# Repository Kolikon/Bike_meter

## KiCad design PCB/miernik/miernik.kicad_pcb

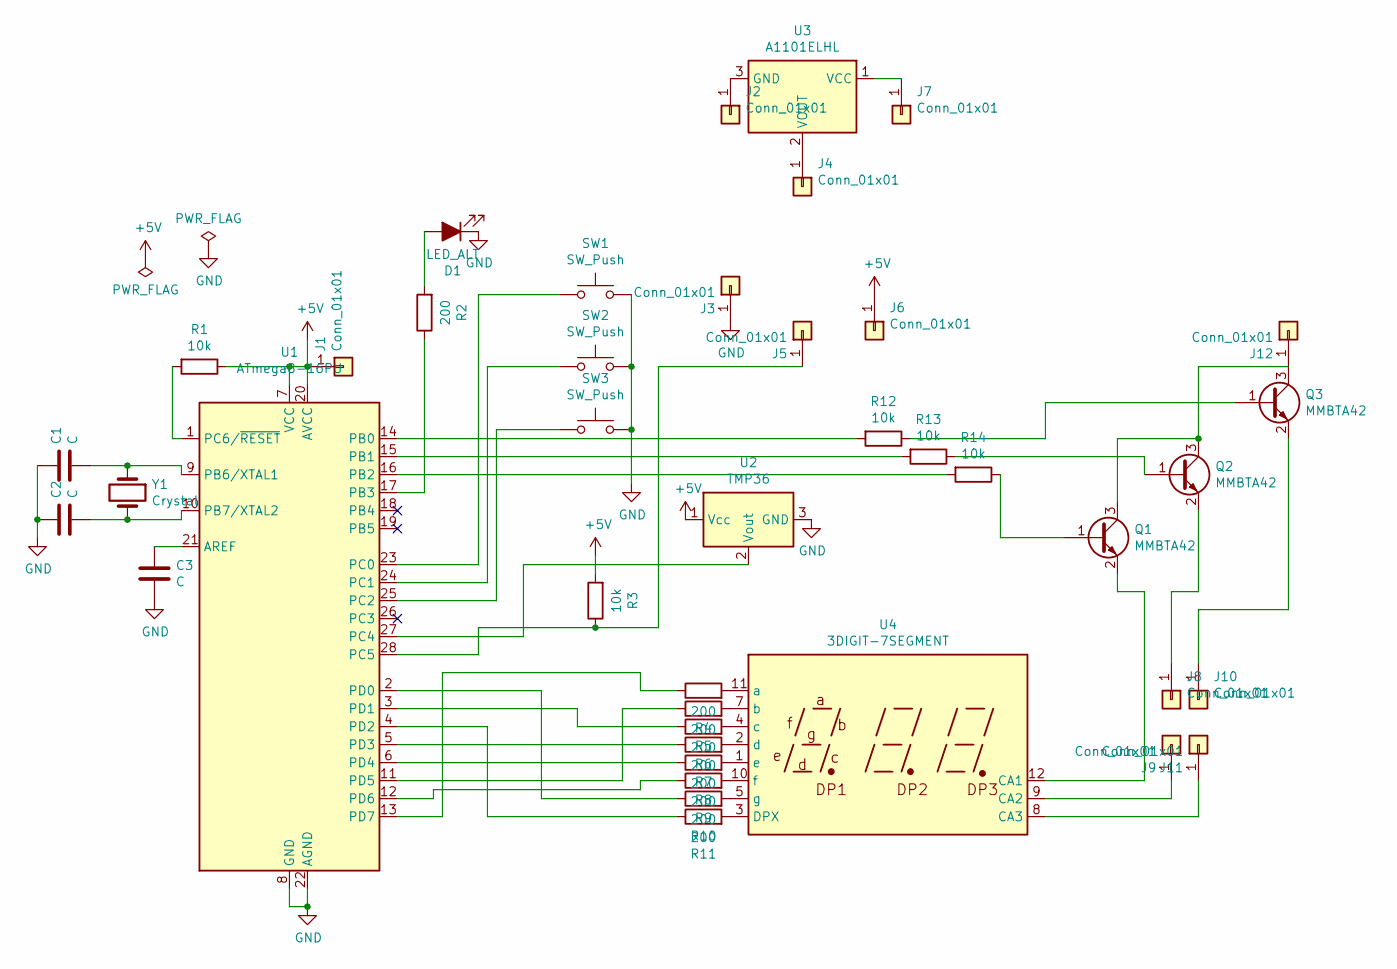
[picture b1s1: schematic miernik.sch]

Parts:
C1, C2: C; C_Disc_D5.0mm_W2.5mm_P5.00mm
C3: C; C_Disc_D7.0mm_W2.5mm_P5.00mm
D1: LED_ALT; LED_D3.0mm
J1, J2, J3, J4, J5, J6, J7, J8, J9, J10, J11, J12: Conn_01x01; SolderWire-0.25sqmm_1x01_D0.65mm_OD1.7mm
Q1, Q2, Q3: MMBTA42; SOT-23
R1, R3, R12, R13, R14: 10k; R_1206_3216Metric
R2, R4, R5, R6, R7, R8, R9, R10, R11: 200; R_1206_3216Metric
SW1, SW2, SW3: SW_Push; SW_PUSH_6mm
U1: ATmega8-16PU; DIP-28_W7.62mm_Socket
U2: TMP36; TO-92
U3: A1101ELHL; TO-92
U4: 3DIGIT-7SEGMENT
Y1: Crystal; Crystal_HC49-4H_Vertical

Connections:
+5V: J1.1, J6.1, R1.1, R3.2, U1.7 (VCC), U1.20 (AVCC), U2.1 (Vcc)
GND: C1.1, C2.1, C3.2, D1.1 (K), J3.1, SW1.2, SW2.2, SW3.2, U1.8 (GND), U1.22 (AGND), U2.3 (GND)
unnamed: C1.2, U1.9 (PB6/XTAL1), Y1.1
unnamed: C2.2, U1.10 (PB7/XTAL2), Y1.2
unnamed: C3.1, U1.21 (AREF)
unnamed: D1.2 (A), R2.2
unnamed: J2.1, U3.3 (GND)
unnamed: J4.1, U3.2 (VOUT)
unnamed: J5.1, R3.1, U1.28 (PC5)
unnamed: J7.1, U3.1 (VCC)
unnamed: J8.1, Q2.2 (E)
unnamed: J9.1, U4.9 (CA2)
unnamed: J10.1, Q3.2 (E)
unnamed: J11.1, U4.8 (CA3)
unnamed: J12.1, Q1.3 (C), Q2.3 (C), Q3.3 (C)
unnamed: Q1.1 (B), R14.1
unnamed: Q1.2 (E), U4.12 (CA1)
unnamed: Q2.1 (B), R13.1
unnamed: Q3.1 (B), R12.1
unnamed: R1.2, U1.1 (PC6/~RESET)
unnamed: R2.1, U1.17 (PB3)
unnamed: R4.1, U1.13 (PD7)
unnamed: R4.2, U4.11 (a)
unnamed: R5.1, U1.11 (PD5)
unnamed: R5.2, U4.7 (b)
unnamed: R6.1, U1.3 (PD1)
unnamed: R6.2, U4.4 (c)
unnamed: R7.1, U1.5 (PD3)
unnamed: R7.2, U4.2 (d)
unnamed: R8.1, U1.6 (PD4)
unnamed: R8.2, U4.1 (e)
unnamed: R9.1, U1.12 (PD6)
unnamed: R9.2, U4.10 (f)
unnamed: R10.1, U1.2 (PD0)
unnamed: R10.2, U4.5 (g)
unnamed: R11.1, U1.4 (PD2)
unnamed: R11.2, U4.3 (DPX)
unnamed: R12.2, U1.14 (PB0)
unnamed: R13.2, U1.15 (PB1)
unnamed: R14.2, U1.16 (PB2)
unnamed: SW1.1, U1.23 (PC0)
unnamed: SW2.1, U1.24 (PC1)
unnamed: SW3.1, U1.25 (PC2)
unnamed: U1.27 (PC4), U2.2 (Vout)

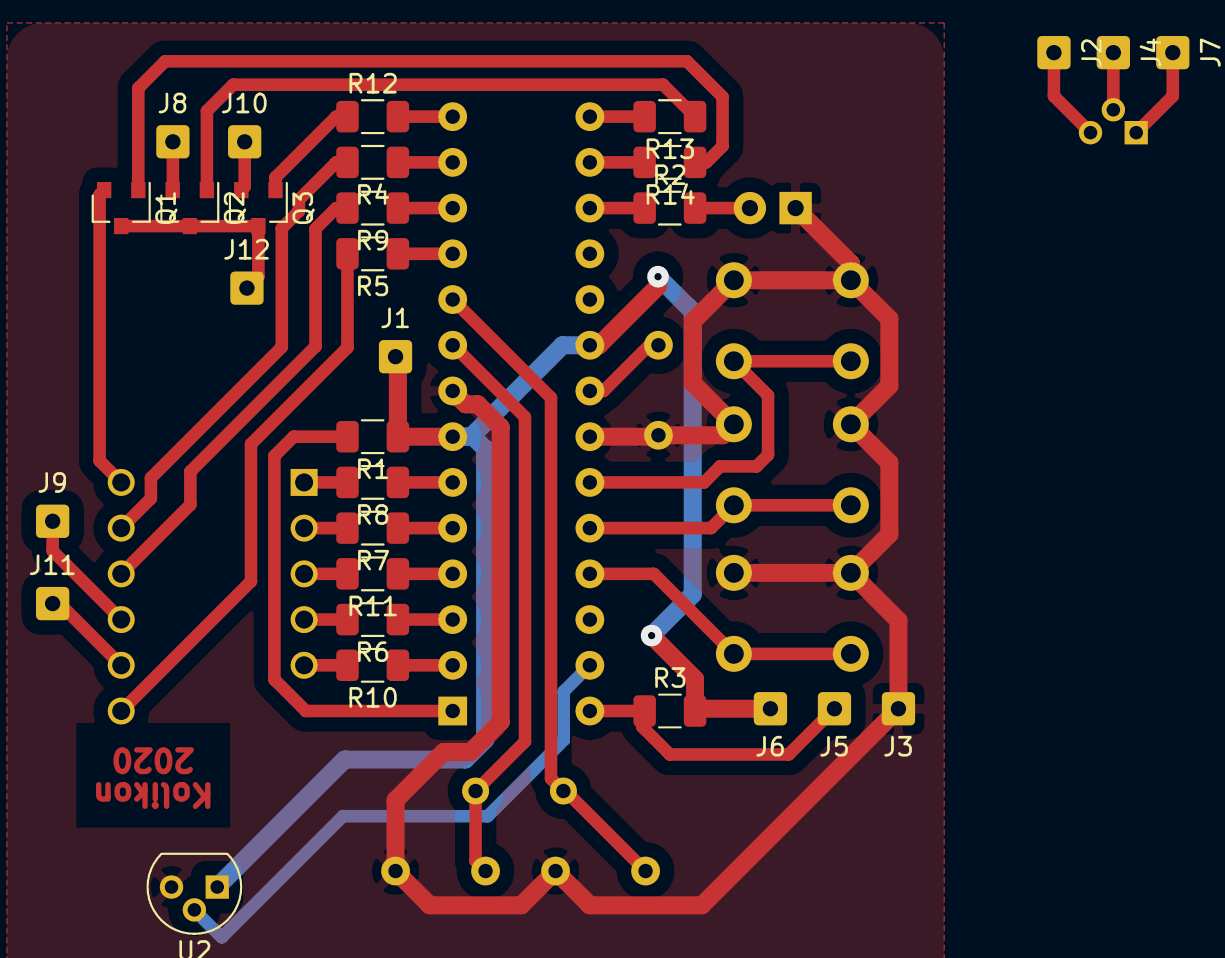
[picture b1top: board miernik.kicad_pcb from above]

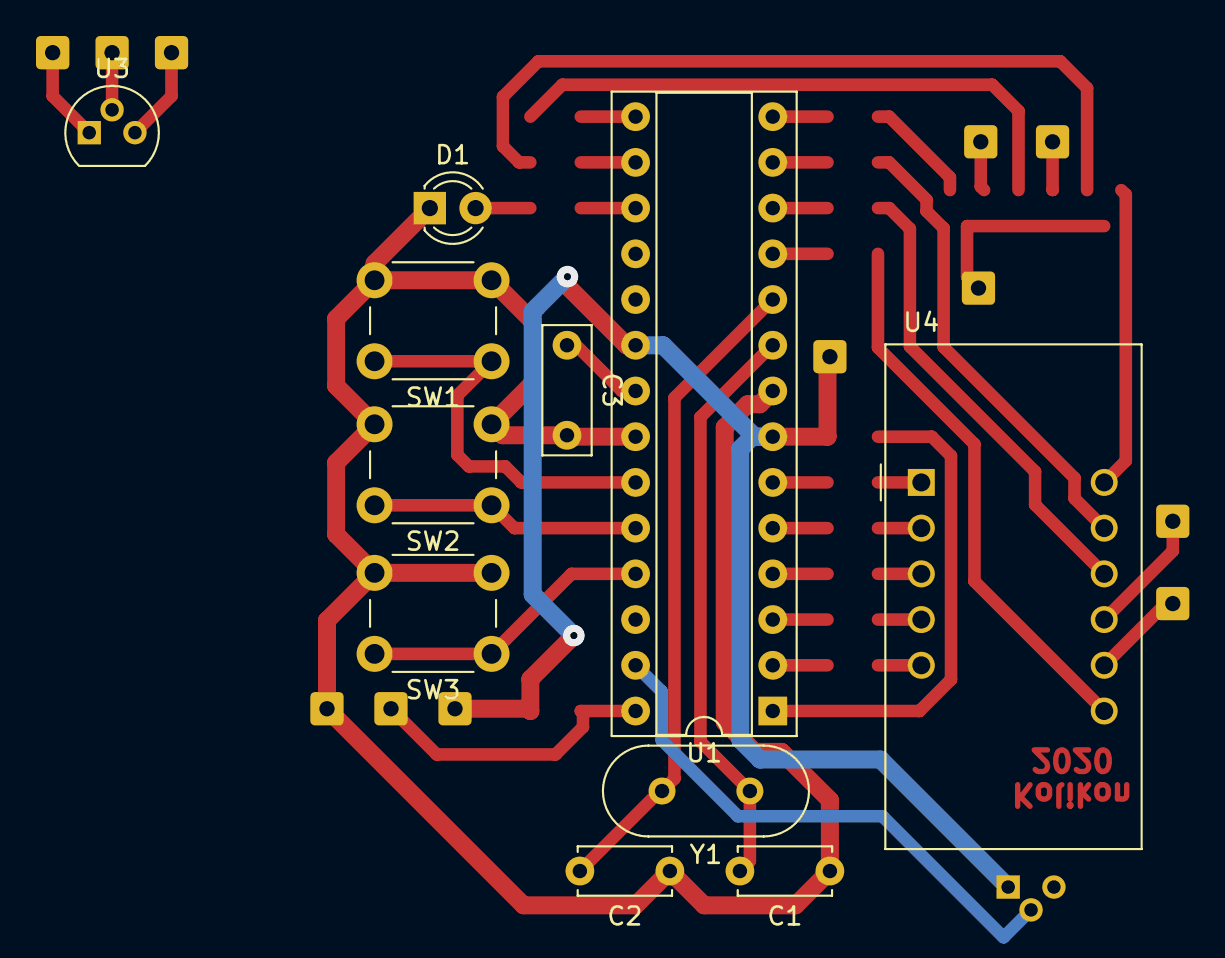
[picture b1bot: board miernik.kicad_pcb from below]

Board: 2 copper layers, 41 parts (11 on the bottom side), 44 nets.

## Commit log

2021-08-29 Add files via upload
    Added temperature sensor, added some letters and names for modes, fixed problem with float in total distance.
